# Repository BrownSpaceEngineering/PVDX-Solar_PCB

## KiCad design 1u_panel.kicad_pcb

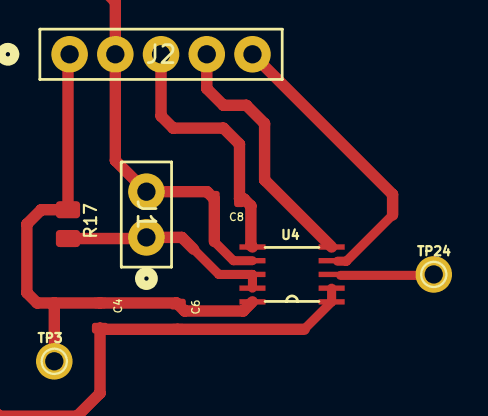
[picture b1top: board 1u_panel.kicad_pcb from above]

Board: 2 copper layers, 9 parts (0 on the bottom side), 7 nets.

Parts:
C4: 10u; .0603-C-NOSILK
C6, C8: 100n; .0603-C-NOSILK
J1: PPPC021LFBN-RC; CONN_PPPC021_SUL
J2: PPTC051LFBN-RC; CONN5_1LFBN-RC_SUL
R17: 0.1 0805; .0805-C-NOSILK
TP3, TP24: TEST-POINT-LARGE-SQUARE; 1X01
U4: INA226AIDGSR; DGS10

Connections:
3.3V: C8.1, J2.3, U4.6 (VS)
GND: C4.2, C6.2, C8.2, J1.2, J2.2, U4.1 (A1), U4.2 (A0), U4.7 (GND)
unnamed: TP24.1, U4.3 (ALERT)
unnamed: J1.1, R17.2, U4.8 (VBUS), U4.9 (VIN-)
SCL: J2.4, U4.5 (SCL)
SDA: J2.5, U4.4 (SDA)
VSOLAR: C4.1, C6.1, J2.1, R17.1, TP3.1, U4.10 (VIN+)

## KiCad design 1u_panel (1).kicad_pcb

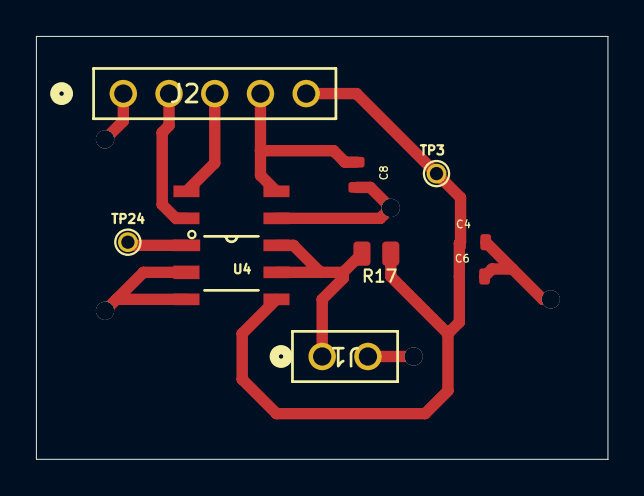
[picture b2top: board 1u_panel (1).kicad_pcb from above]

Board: 2 copper layers, 31.8 x 23.5 mm, 9 parts (0 on the bottom side), 7 nets.

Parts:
C4: 10u; .0603-C-NOSILK
C6, C8: 100n; .0603-C-NOSILK
J1: PPPC021LFBN-RC; CONN_PPPC021_SUL
J2: PPTC051LFBN-RC; CONN5_1LFBN-RC_SUL
R17: 0.1 0805; .0805-C-NOSILK
TP3, TP24: TEST-POINT-LARGE-SQUARE; 1X01
U4: INA226AIDGSR; DGS10

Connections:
3.3V: C8.1, J2.4, U4.6 (VS)
GND: C4.2, C6.2, C8.2, J1.2, J2.1, U4.1 (A1), U4.2 (A0), U4.7 (GND)
unnamed: TP24.1, U4.3 (ALERT)
unnamed: J1.1, R17.2, U4.8 (VBUS), U4.9 (VIN-)
SCL: J2.3, U4.5 (SCL)
SDA: J2.2, U4.4 (SDA)
VSOLAR: C4.1, C6.1, J2.5, R17.1, TP3.1, U4.10 (VIN+)

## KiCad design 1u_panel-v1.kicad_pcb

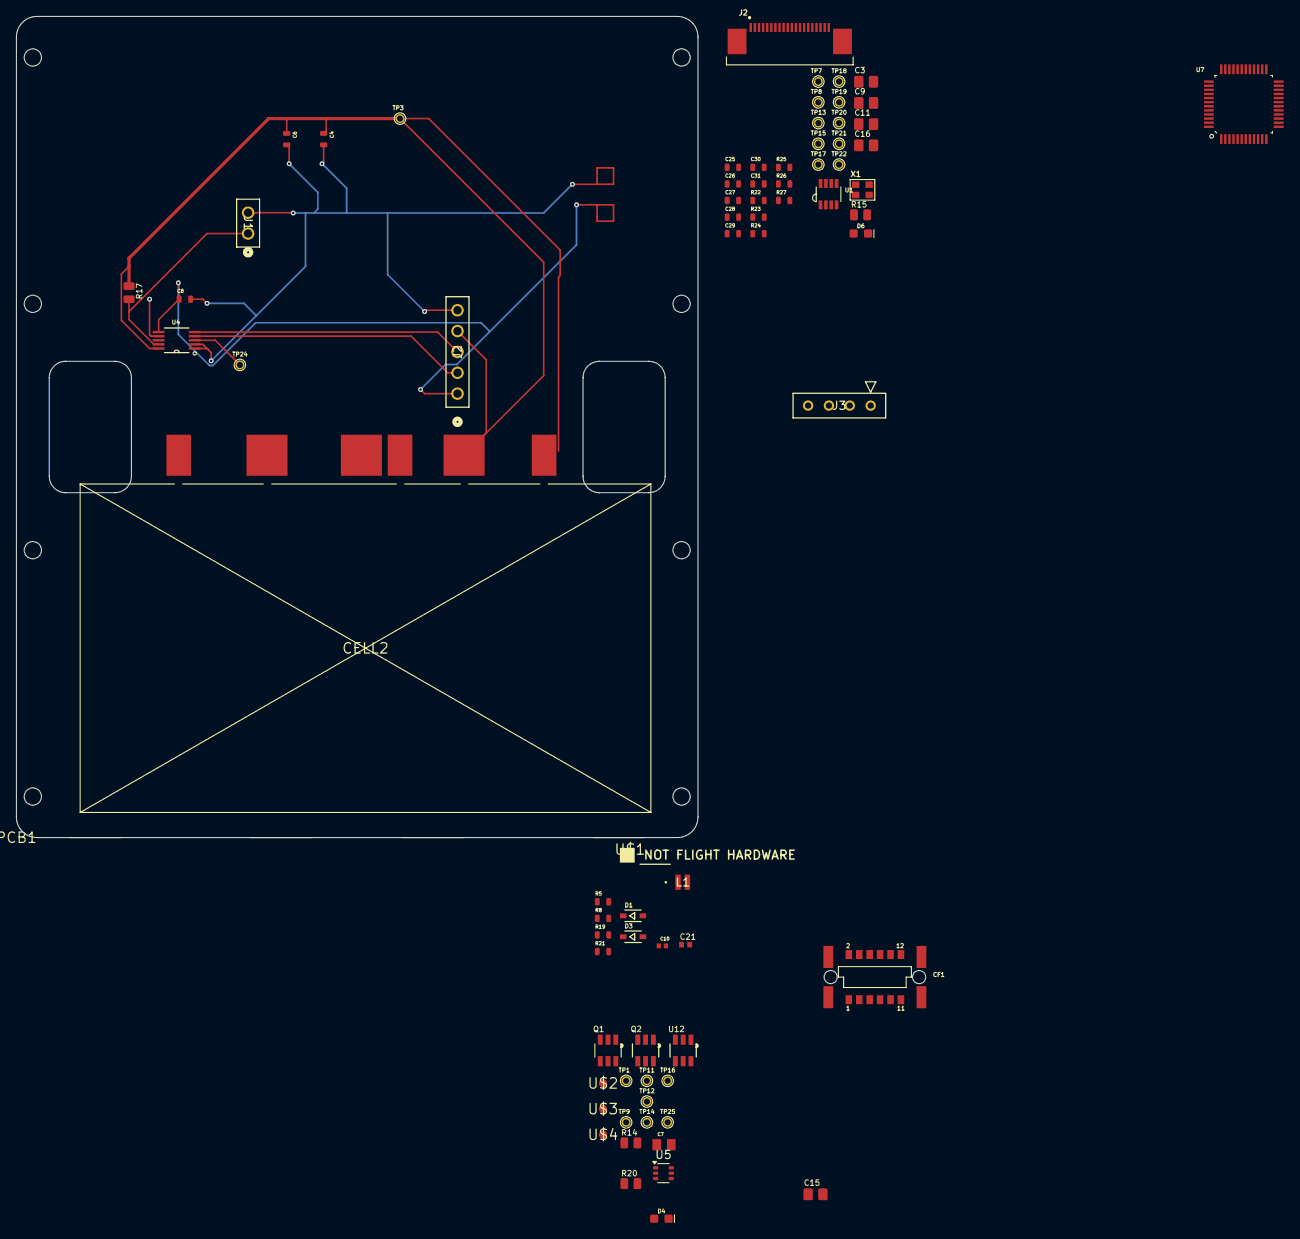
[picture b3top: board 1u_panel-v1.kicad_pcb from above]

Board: 2 copper layers, 83.0 x 100.0 mm, 75 parts (0 on the bottom side), 49 nets.

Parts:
C3, C9, C11, C15, C16: 22u; .0805-B-NOSILK
C4: 10u; .0603-C-NOSILK
C6, C8, C25, C26, C29, C30, C31: 100n; .0603-C-NOSILK
C7: GRM219R60J106KE19D; CAPC2012X95N
C10: GRM155R70J105KA12D; CAPC1005X55N
C21: 100n; .0402-B-NOSILK
C27, C28: 20p; .0603-C-NOSILK
CELL2: SPECTROLAB-XTE-SF
CF1: M55-6021242R; HARWIN-M55-60X1242R
D1, D3: 1N4151WS; SOD323-R
D4: GREEN; LED-0603
D6: AMBER; LED-0603
J1: PPPC021LFBN-RC; CONN_PPPC021_SUL
J2: PPTC051LFBN-RC; CONN5_1LFBN-RC_SUL
J2#2: 2-1734592-0; J-TE-2-1734592-0
J3: PPTC041LFBN-RC; CONN_PPTC041LFBN-RC_SUL
L1: XFL2010-682MEC; IND_XFL2010_COC
PCB1: ORESAT-SOLAR-BOARD-V4-SPECTROLABS; ORESAT-SOLAR-BOARD-V4
Q1: DMP3050LVT-7; SOT23-6
Q2: DMP2240UDM-7; SOT23-6
R5: 200k; .0603-C-NOSILK
R8, R19: 100k; .0603-C-NOSILK
R14, R15, R20: 0; .0805-C-NOSILK
R17: 0.1 0805; .0805-C-NOSILK
R21, R23: 2.7k; .0603-C-NOSILK
R22: 10k; .0603-C-NOSILK
R24, R25, R26, R27: 1k/NP; .0603-C-NOSILK
TP1, TP3, TP7, TP8, TP9, TP11, TP12, TP13, TP14, TP15, TP16, TP17, TP18, TP19, TP20, TP21, TP22, TP24, TP25: TEST-POINT-LARGE-SQUARE; 1X01
U1: TCAN330GDCNT; SOT23-8_TI-DCN
U4: INA226AIDGSR; DGS10
U5: LTC3525D-3.3; SOT-363_SC-70-6
U7: STM32F091CCT7; STM32F091C
U12: LTC4412; SOT23-6
U$1: FLIGHMARKERNEW; FLIGHTMARKER_NEW_BOARDS
U$2, U$3, U$4: FIDUCIAL; FIDUCIAL_1MM
X1: ECS-160-10-36Q-ES-TR; CRYSTAL_2.5X2

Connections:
3.3V: C3.1, C8.1, C9.1, C11.1, C16.1, C25.2, C26.2, C29.2, C30.2, C31.2, J2.1, J2#2.11 (VTARGET), R15.1, R20.1, R21.1, U1.3 (VCC), U4.6 (VS), U7.1 (VBAT), U7.9 (VDDA), U7.24 (VDD), U7.36 (VDDIO2), U7.48 (VDD)
/1u_panel-microcontroller/BOOT0: R22.1, TP7.1, U7.44 (PF11-BOOT0)
/1u_panel-microcontroller/CAN_RX: U1.4 (RXD), U7.32 (PA11)
/1u_panel-microcontroller/CAN_SHDN: U1.5 (SHDN), U7.31 (PA10)
/1u_panel-microcontroller/CAN_SILENT: U1.8 (S), U7.30 (PA9)
/1u_panel-microcontroller/CAN_TX: U1.1 (TXD), U7.33 (PA12)
/1u_panel-microcontroller/NRESET: J2#2.10 (NRST), TP13.1, U7.7 (NRST)
/1u_panel-microcontroller/PA0: R23.2, U7.10 (PA0)
/1u_panel-microcontroller/PA2/USART2_TX: J2#2.13 (CARD-TX), U7.12 (PA2)
/1u_panel-microcontroller/PA3/USART2_RX: J2#2.12 (CARD-RX), U7.13 (PA3)
/1u_panel-microcontroller/SMSN0: R24.1, U7.25 (PB12)
/1u_panel-microcontroller/SMSN1: R25.1, U7.26 (PB13)
/1u_panel-microcontroller/SMSN2: R26.1, U7.27 (PB14)
/1u_panel-microcontroller/SMSN3: R27.1, U7.28 (PB15)
/1u_panel-microcontroller/SWCLK: J2#2.15 (SWCLK), U7.37 (PA14-SWCLK)
/1u_panel-microcontroller/SWDIO: J2#2.14 (SWDIO), U7.34 (PA13-SWDIO)
/1u_panel-power/~SHDN-3.3V: D1.A, R5.2, TP9.1
/1u_panel-power/~SHDN-OUPUT: D3.A, Q1.3 (G), R19.1, TP25.1
/1u_panel-power/~SHUTDOWN: CF1.1 (~SD), CF1.2 (~SD), D1.C, D3.C, TP11.1
CANH: CF1.9 (CANH), CF1.10 (CANH), U1.7 (CANH)
CANL: CF1.11 (CANL), CF1.12 (CANL), U1.6 (CANL)
GND: C3.2, C4.2, C6.2, C7.1, C8.2, C9.2, C10.1, C11.2, C15.2, C16.2, C21.2, C25.1, C26.1, C27.2, C28.2, C29.1, C30.1, C31.1, CELL2.NEG1 (C1), CELL2.NEG2 (C2), CELL2.NEG3 (C3), CELL2.NEG4 (C4), CF1.3 (GND), CF1.4 (GND), CF1.P$1 (SHIELD), CF1.P$2 (SHIELD), CF1.P$3 (SHIELD), CF1.P$4 (SHIELD), D4.C, D6.C, J1.2, J2.5, J2#2.3 (GND), J2#2.6 (GND), J2#2.9 (GND), J3.4, R8.1, R22.2, R24.2, R25.2, R26.2, R27.2, U1.2 (GND), U4.1 (A1), U4.2 (A0), U4.7 (GND), U5.2 (GND), U5.5 (GND), U7.8 (VSSA), U7.23 (VSS), U7.35 (VSS), U7.47 (VSS), U12.2 (GND), X1.2 (SHIELD), X1.4 (SHIELD)
unnamed: CF1.7 (AUX), CF1.8 (AUX), TP1.1
unnamed: D4.A, R21.2
unnamed: D6.A, R23.1
unnamed: J2#2.17 (DEBUG-0), TP17.1
unnamed: J2#2.18 (DEBUG-1), R15.2, TP18.1
unnamed: J2#2.19 (DEBUG-2), TP19.1
unnamed: J2#2.20 (DEBUG-3), TP20.1
unnamed: J2#2.16 (SWO), TP21.1
unnamed: J2#2.1 (VBUSP), J2#2.2 (VBUSP), TP8.1
unnamed: Q2.1 (G), Q2.3 (G), U12.5 (GATE)
unnamed: Q2.2 (S), Q2.5 (S)
unnamed: TP24.1, U4.3 (ALERT)
unnamed: J1.1, R17.2, U4.8 (VBUS), U4.9 (VIN-)
unnamed: L1.1, U5.6 (SW)
unnamed: C10.2, L1.2, R14.1, U5.3 (VIN)
unnamed: C7.2, C15.1, R20.2, U5.4 (VOUT)
unnamed: R5.1, R8.2, U5.1 (~SHDN)
unnamed: TP15.1, U7.15 (PA5)
unnamed: TP22.1, U7.16 (PA6)
unnamed: C28.1, U7.5 (PF0-OSC_IN), X1.1
unnamed: C27.1, U7.6 (PF1-OSC_OUT), X1.3 (2)
unnamed: Q1.1 (D), Q1.2 (D), Q1.5 (D), Q1.6 (D), U12.3 (CTL)
unnamed: TP16.1, U12.4 (STAT)
SCL: J2.3, J3.2, U4.5 (SCL), U7.21 (PB10)
SDA: J2.2, J3.1, U4.4 (SDA), U7.22 (PB11)
VBUS: CF1.5 (VBUS), CF1.6 (VBUS), Q2.6 (D), TP14.1, U12.6 (SENSE)
VSOLAR: C4.1, C6.1, C21.1, CELL2.POS1 (A1), CELL2.POS2 (A2), J2.4, Q1.4 (S), Q2.4 (D), R14.2, R17.1, R19.2, TP3.1, TP12.1, U4.10 (VIN+), U12.1 (VIN)

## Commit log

2025-11-16 Add files via upload
    Modified panel level of the original orseat board to swap out the TPS63060 for the LTC3525D-3.3
2025-11-23 Add files via upload
    Schematic completed and layout generated with no errors
2025-11-23 Update schematic.
2025-11-26 Add files via upload
    First try at Layout
2026-01-25 Layout draft
    Note that there's currently no footprint for the panels; need to make one based on the panels we have in storage
2026-02-08 MOST RECENT PCB LAYOUT
2026-02-13 MOST RECENT SOLAR LAYOUT
